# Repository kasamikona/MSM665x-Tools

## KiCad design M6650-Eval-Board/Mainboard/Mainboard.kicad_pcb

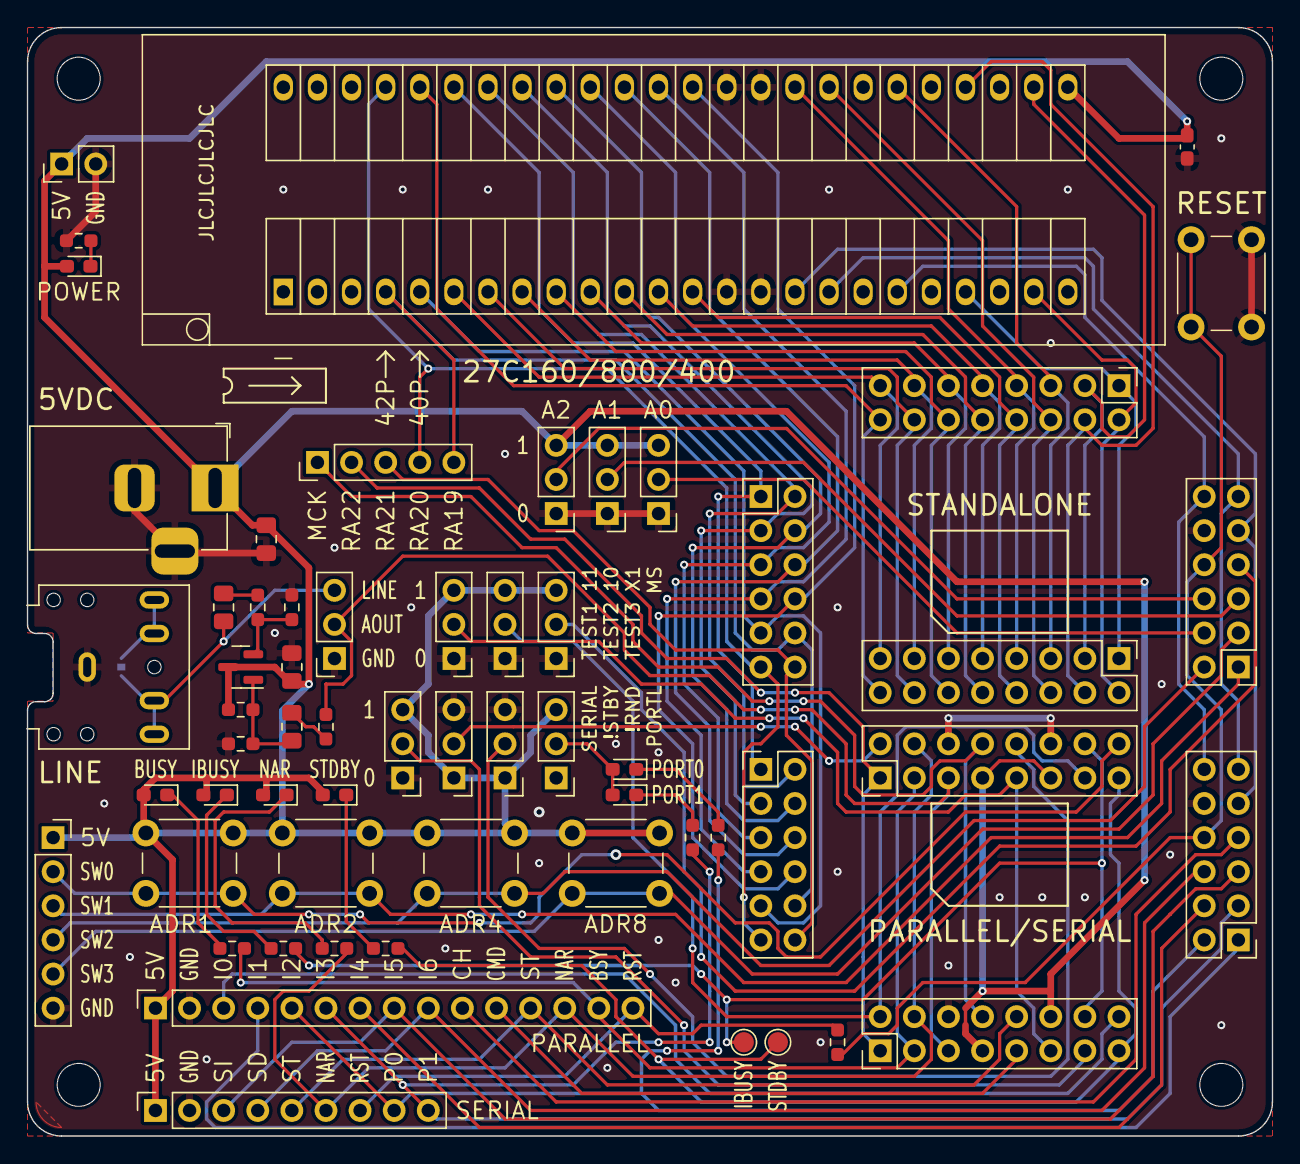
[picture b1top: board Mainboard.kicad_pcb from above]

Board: 2 copper layers, 92.7 x 82.6 mm, 65 parts (1 on the bottom side), 79 nets.

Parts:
C1, C4, C5: 10u; C_0805_2012Metric_Pad1.18x1.45mm_HandSolder
C2: 100n; C_0603_1608Metric_Pad1.08x0.95mm_HandSolder
C3: 1u; C_0805_2012Metric_Pad1.18x1.45mm_HandSolder
D1: BUSY; LED_0603_1608Metric_Pad1.05x0.95mm_HandSolder
D2: IBUSY; LED_0603_1608Metric_Pad1.05x0.95mm_HandSolder
D3: NAR; LED_0603_1608Metric_Pad1.05x0.95mm_HandSolder
D4: STANDBY; LED_0603_1608Metric_Pad1.05x0.95mm_HandSolder
D5: POWER; LED_0603_1608Metric_Pad1.05x0.95mm_HandSolder
D6: PORT0; LED_0603_1608Metric_Pad1.05x0.95mm_HandSolder
D7: PORT1; LED_0603_1608Metric_Pad1.05x0.95mm_HandSolder
H1, H2, H3, H4: MountingHole; MountingHole_3.2mm_M3
J1: MB; PinHeader_2x08_P2.54mm_Vertical
J2: MR; PinHeader_2x06_P2.54mm_Vertical
J3: MT; PinHeader_2x08_P2.54mm_Vertical
J4: ML; PinHeader_2x06_P2.54mm_Vertical
J5: SB; PinHeader_2x08_P2.54mm_Vertical
J6: SR; PinHeader_2x06_P2.54mm_Vertical
J7: ST; PinHeader_2x08_P2.54mm_Vertical
J8: SL; PinHeader_2x06_P2.54mm_Vertical
J9: Buttons; PinSocket_1x06_P2.54mm_Vertical
J10: Parallel; PinSocket_1x15_P2.54mm_Vertical
J11: Serial; PinSocket_1x09_P2.54mm_Vertical
J12: 5V; BarrelJack_Horizontal
J13: 5V; PinHeader_1x02_P2.54mm_Vertical
J14: Misc; PinHeader_1x05_P2.54mm_Vertical
J15: Line Out; Jack_3.5mm_PJ307_Horizontal
J16: AUD; PinSocket_1x03_P2.54mm_Vertical
JP1: TEST1; PinHeader_1x03_P2.54mm_Vertical
JP2: TEST2; PinHeader_1x03_P2.54mm_Vertical
JP3: TEST3; PinHeader_1x03_P2.54mm_Vertical
JP4: A0; PinHeader_1x03_P2.54mm_Vertical
JP5: A1; PinHeader_1x03_P2.54mm_Vertical
JP6: A2; PinHeader_1x03_P2.54mm_Vertical
JP7: RND; PinHeader_1x03_P2.54mm_Vertical
JP8: SERIAL; PinHeader_1x03_P2.54mm_Vertical
JP9: PORTL; PinHeader_1x03_P2.54mm_Vertical
JP10: STBY; PinHeader_1x03_P2.54mm_Vertical
JP11: TRS; SolderJumper-2_P1.3mm_Bridged_RoundedPad1.0x1.5mm
Q1: MMBT3904; SOT-23
R1, R2, R3, R4, R5, R6, R7: 10K; R_0603_1608Metric_Pad0.98x0.95mm_HandSolder
R8, R9, R10: 100K; R_0603_1608Metric_Pad0.98x0.95mm_HandSolder
R11: 1K; R_0603_1608Metric_Pad0.98x0.95mm_HandSolder
R12, R13: 100R; R_0603_1608Metric_Pad0.98x0.95mm_HandSolder
SW1: P01; SW_PUSH_6mm_H5mm
SW2: P02; SW_PUSH_6mm_H5mm
SW3: P04; SW_PUSH_6mm_H5mm
SW4: P08; SW_PUSH_6mm_H5mm
SW5: RESET; SW_PUSH_6mm_H5mm
TP1: IBUSY; TestPoint_Pad_D1.5mm
TP2: STANDBY; TestPoint_Pad_D1.5mm
U1: 27C160; ZIF-Socket-48P

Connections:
/5V: C1.1, C2.1, C5.1, D1.2 (A), D2.2 (A), D3.2 (A), D4.2 (A), D5.2 (A), J1.7, J1.12, J5.7, J5.11, J9.1, J10.1, J11.1, J12.1, J13.1, JP1.3 (B), JP2.3 (B), JP3.3 (B), JP4.3 (B), JP5.3 (B), JP6.3 (B), JP7.1 (A), JP8.3 (B), JP9.3 (B), JP10.1 (A), Q1.3 (C), R9.1, SW1.1, SW2.1, SW3.1, SW4.1, U1.25 (VCC)
/A0: J6.4, JP4.2 (C)
/A1: J6.5, JP5.2 (C)
/A2: J6.6, JP6.2 (C)
/AOUT: J1.5, J5.5, J16.2, R8.1
/BUSY: J1.3, J5.3, J10.14, R1.2
/CE: J2.9, J6.9, U1.16 (~OE)
/CH: J2.7, J10.10
/CMD: J1.9, J10.11
/D0: J2.11, J6.11, U1.17 (Q0)
/D1: J2.12, J6.12, U1.19 (Q1)
/D2: J3.1, J7.1, U1.21 (Q2)
/D3: J3.2, J7.2, U1.23 (Q3)
/D4: J3.3, J7.3, U1.26 (Q4)
/D5: J3.4, J7.4, U1.28 (Q5)
/D6: J3.5, J7.5, U1.30 (Q6)
/D7: J3.6, J7.6, U1.32 (Q7)
/GND: C1.2, C2.2, C5.2, J1.6, J2.10, J5.6, J5.12, J6.10, J9.6, J10.2, J11.2, J12.2, J12.3, J13.2, J15.S, J16.1, JP1.1 (A), JP2.1 (A), JP3.1 (A), JP4.1 (A), JP5.1 (A), JP6.1 (A), JP7.3 (B), JP8.1 (A), JP10.3 (B), R5.2, R10.2, R11.2, SW5.1, U1.14 (~CE), U1.15 (VSS), U1.34 (VSS), U1.35 (~BYTE/VPP)
/I0: J1.16, J10.3
/I1: J2.1, J10.4
/I2P0: J2.2, J10.5, J11.8, R6.1
/I3P1: J2.3, J10.6, J11.9, R7.1
/I4: J2.4, J10.7
/I5SI: J2.5, J10.8, J11.3
/I6SD: J2.6, J10.9, J11.4
/IBUSY: J1.14, J5.14, R2.2, TP1.1
/MCK: J1.8, J5.8, J14.1
/NAR: J1.4, J5.4, J10.13, J11.6, R3.2
/RA0: J3.7, J7.7, U1.33 (Q15/A-1)
/RA1: J3.8, J7.8, U1.13 (A0)
/RA2: J3.9, J7.9, U1.12 (A1)
/RA3: J3.10, J7.10, U1.11 (A2)
/RA4: J3.11, J7.11, U1.10 (A3)
/RA5: J3.12, J7.12, U1.9 (A4)
/RA6: J3.13, J7.13, U1.8 (A5)
/RA7: J3.14, J7.14, U1.7 (A6)
/RA8: J3.15, J7.15, U1.6 (A7)
/RA9: J3.16, J7.16, U1.44 (A8)
/RA10: J4.1, J8.1, U1.43 (A9)
/RA11: J4.2, J8.2, U1.42 (A10)
/RA12: J4.3, J8.3, U1.41 (A11)
/RA13: J4.4, J8.4, U1.40 (A12)
/RA14: J4.5, J8.5, U1.39 (A13)
/RA15: J4.6, J8.6, U1.38 (A14)
/RA16: J4.7, J8.7, U1.37 (A15)
/RA17: J4.8, J8.8, U1.36 (A16)
/RA18: J4.9, J8.9, U1.5 (A17)
/RA19: J4.10, J8.10, J14.5, U1.4 (A18)
/RA20: J4.11, J8.11, J14.4, U1.45 (A19)
/RA21: J4.12, J8.12, J14.3
/RA22: J1.1, J5.1, J14.2
/RESET: J2.8, J6.8, R13.1, SW5.2
/RESETR: J10.15, J11.7, R13.2
/RND: J5.10, JP7.2 (C)
/SERIAL: J1.13, JP8.2 (C)
/ST: J1.10, J10.12, J11.5
/STANDBY: J1.15, J5.15, R4.2, TP2.1
/STBY: J5.2, JP10.2 (C)
/SW0: J5.16, J9.2, SW1.2
/SW1: J6.1, J9.3, SW2.2
/SW2: J6.2, J9.4, SW3.2
/SW3: J6.3, J9.5, SW4.2
/TEST1: J1.11, J5.9, JP1.2 (C)
/TEST2: J1.2, J5.13, JP2.2 (C)
/TEST3: J6.7, JP3.2 (C)
unnamed: C3.1, R8.2
unnamed: C4.1, R12.2
unnamed: D1.1 (K), R1.1
unnamed: D2.1 (K), R2.1
unnamed: D3.1 (K), R3.1
unnamed: D4.1 (K), R4.1
unnamed: D5.1 (K), R5.1
unnamed: D6.2 (A), D7.2 (A), JP9.2 (C)
unnamed: D6.1 (K), R6.2
unnamed: D7.1 (K), R7.2
unnamed: C4.2, J15.T, J15.TN, J16.3, JP11.1 (A)
unnamed: J15.R, J15.RN, JP11.2 (B)
unnamed: C3.2, Q1.1 (B), R9.2, R10.1
unnamed: Q1.2 (E), R11.1, R12.1

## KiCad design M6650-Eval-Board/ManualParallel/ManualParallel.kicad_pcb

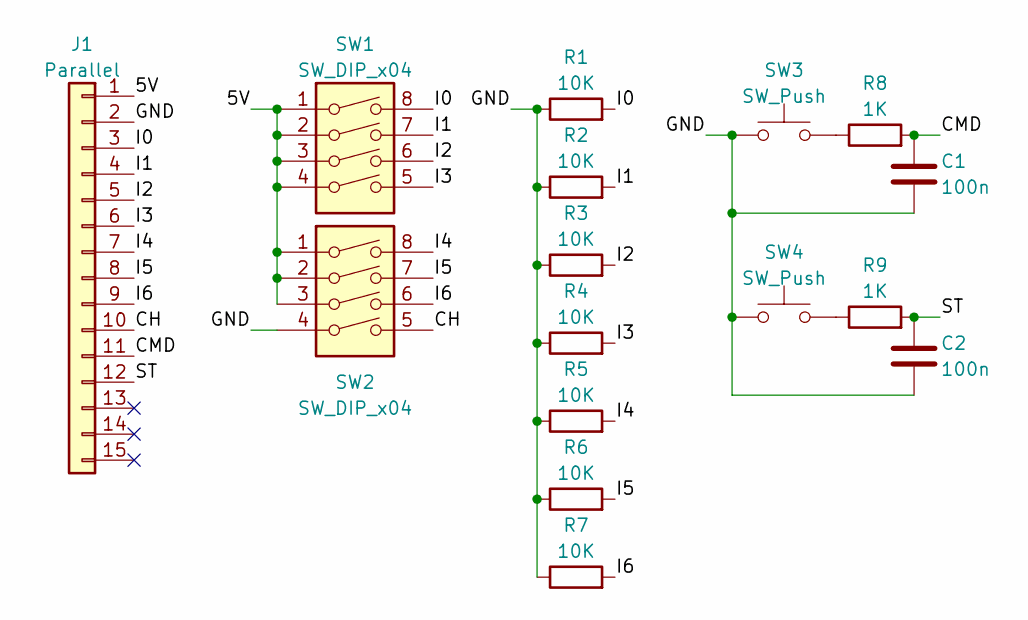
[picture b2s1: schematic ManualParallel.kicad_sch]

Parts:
C1, C2: 100n; C_0603_1608Metric_Pad1.08x0.95mm_HandSolder
J1: Parallel; PinHeader_1x15_P2.54mm_Vertical
R1, R2, R3, R4, R5, R6, R7: 10K; R_0603_1608Metric_Pad0.98x0.95mm_HandSolder
R8, R9: 1K; R_0603_1608Metric_Pad0.98x0.95mm_HandSolder
SW1, SW2: SW_DIP_x04; SW_DIP_SPSTx04_Slide_9.78x12.34mm_W7.62mm_P2.54mm
SW3, SW4: SW_Push; SW_PUSH_6mm_H5mm

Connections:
/5V: J1.1, SW1.1, SW1.2, SW1.3, SW1.4, SW2.1, SW2.2, SW2.3
/CH: J1.10, SW2.5
/CMD: C1.1, J1.11, R8.2
/GND: C1.2, C2.2, J1.2, R1.1, R2.1, R3.1, R4.1, R5.1, R6.1, R7.1, SW2.4, SW3.1, SW4.1
/I0: J1.3, R1.2, SW1.8
/I1: J1.4, R2.2, SW1.7
/I2: J1.5, R3.2, SW1.6
/I3: J1.6, R4.2, SW1.5
/I4: J1.7, R5.2, SW2.8
/I5: J1.8, R6.2, SW2.7
/I6: J1.9, R7.2, SW2.6
/ST: C2.1, J1.12, R9.2
unnamed: R8.1, SW3.2
unnamed: R9.1, SW4.2

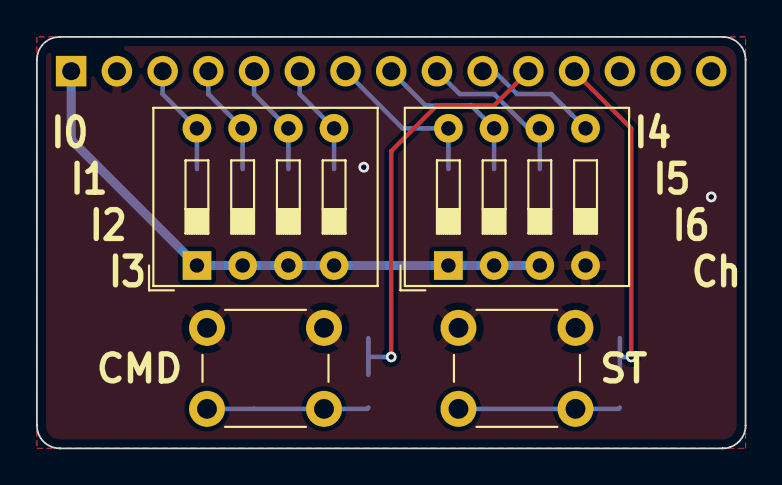
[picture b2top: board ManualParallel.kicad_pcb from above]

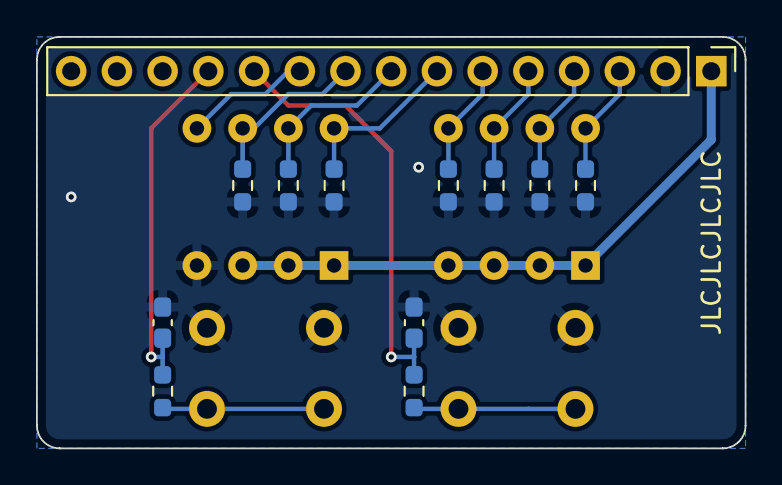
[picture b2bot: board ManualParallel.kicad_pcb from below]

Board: 2 copper layers, 39.4 x 22.9 mm, 16 parts (12 on the bottom side), 14 nets.

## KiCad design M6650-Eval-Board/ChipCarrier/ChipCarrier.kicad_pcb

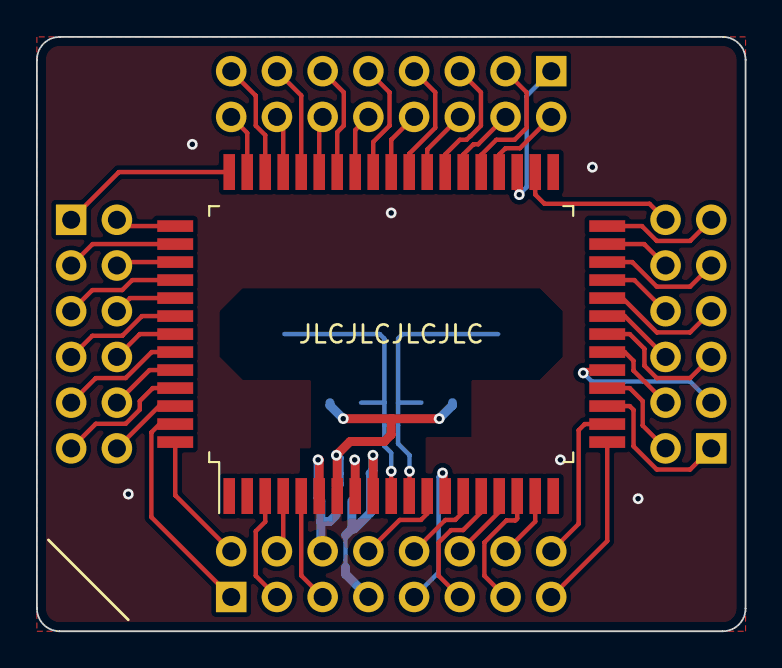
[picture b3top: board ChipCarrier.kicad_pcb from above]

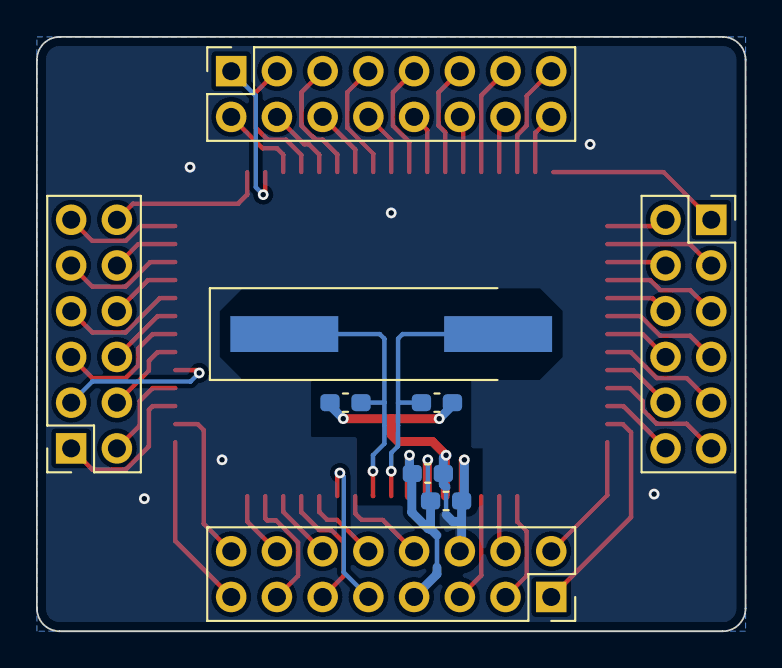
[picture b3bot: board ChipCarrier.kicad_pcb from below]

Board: 2 copper layers, 39.4 x 33.0 mm, 10 parts (9 on the bottom side), 58 nets.

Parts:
C1, C2: 100n; C_0603_1608Metric_Pad1.08x0.95mm_HandSolder
C3, C4: 22p; C_0603_1608Metric_Pad1.08x0.95mm_HandSolder
J1: BB; PinSocket_2x08_P2.54mm_Vertical
J2: BR; PinSocket_2x06_P2.54mm_Vertical
J3: BT; PinSocket_2x08_P2.54mm_Vertical
J4: BL; PinSocket_2x06_P2.54mm_Vertical
U1: MSM6650GS-BK; QFP64-P-1420-1.00-BK
Y1: 4.096M; Crystal_SMD_HC49-SD_HandSoldering

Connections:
/AOUT: J1.5, U1.5 (AOUT)
/BUSY: J1.3, U1.3 (~BUSY)
/CE: J2.9, U1.30 (~CE)
/CH_TEST3: J2.7, U1.28 (~CH/~TEST3)
/CMD_TEST1: J1.9, U1.13 (CMD/~TEST1)
/CPU: J1.12, U1.16 (CPU)
/D0: J2.11, U1.32 (D0)
/D1: J2.12, U1.34 (D1)
/D2: J3.1, U1.35 (D2)
/D3: J3.2, U1.36 (D3)
/D4: J3.3, U1.37 (D4)
/D5: J3.4, U1.38 (D5)
/D6: J3.5, U1.39 (D6)
/D7: J3.6, U1.40 (D7)
/GND: C1.2, C2.2, C3.2, C4.2, J1.6, U1.6 (AGND), U1.7 (DGND)
/I0: J1.16, U1.21 (I0/SW0)
/I1: J2.1, U1.22 (I1/SW1)
/I2: J2.2, U1.23 (I2/PORT0/SW2)
/I3: J2.3, U1.24 (I3/PORT1/SW3)
/I4: J2.4, U1.25 (I4/A0)
/I5: J2.5, U1.26 (I5/SI/A1)
/I6: J2.6, U1.27 (I6/SD/A2)
/IBUSY: J1.14, U1.18 (~IBUSY)
/MCK: J1.8, U1.12 (MCK/OSC3)
/NAR: J1.4, U1.4 (NAR)
/RA0: J3.7, U1.41 (RA0)
/RA1: J3.8, U1.42 (RA1)
/RA2: J3.9, U1.43 (RA2)
/RA3: J3.10, U1.44 (RA3)
/RA4: J3.11, U1.45 (RA4)
/RA5: J3.12, U1.46 (RA5)
/RA6: J3.13, U1.47 (RA6)
/RA7: J3.14, U1.48 (RA7)
/RA8: J3.15, U1.49 (RA8)
/RA9: J3.16, U1.50 (RA9)
/RA10: J4.1, U1.51 (RA10)
/RA11: J4.2, U1.52 (RA11)
/RA12: J4.3, U1.53 (RA12)
/RA13: J4.4, U1.54 (RA13)
/RA14: J4.5, U1.55 (RA14)
/RA15: J4.6, U1.56 (RA15)
/RA16: J4.7, U1.57 (RA16)
/RA17: J4.8, U1.58 (RA17)
/RA18: J4.9, U1.59 (RA18)
/RA19: J4.10, U1.60 (RA19)
/RA20: J4.11, U1.61 (RA20)
/RA21: J4.12, U1.62 (RA21)
/RA22: J1.1, U1.63 (RA22)
/RCS: J2.10, U1.31 (~RCS)
/RESET: J2.8, U1.29 (~RESET)
/SERIAL_TEST2: J1.13, U1.17 (SERIAL/TEST2)
/STANDBY: J1.15, U1.20 (~STANDBY)
/ST_RND: J1.10, U1.14 (~ST/~RND)
/TEST1_XTCR: J1.11, U1.15 (~TEST1/XT/~CR)
/TEST2_STBY: J1.2, U1.64 (~TEST2/~STBY)
/VDD: C1.1, C2.1, J1.7, U1.8 (AVDD), U1.9 (DVDD)
/XI: C4.1, U1.10 (XT/OSC1), Y1.2
/XO: C3.1, U1.11 (~XT/OSC2), Y1.1

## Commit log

2023-05-23 Add initial data
2023-05-23 Oops that's not meant to be md
2023-07-08 Add datasheet and a custom '6650 eval board design (untested)
2023-07-08 Fix a dumb error on eval board extras
2023-07-09 I screwed up some jumper high/low states but not rerouting now so just silkscreen edit
2024-05-31 Update eval board schematic consistency
2024-05-31 Fix XTCR pin for standalone mode
2024-06-02 Improve line-out amplifier for high-impedance DAC output
2024-06-02 Add debounce to manual parallel board, redo board edges and clearance rules
